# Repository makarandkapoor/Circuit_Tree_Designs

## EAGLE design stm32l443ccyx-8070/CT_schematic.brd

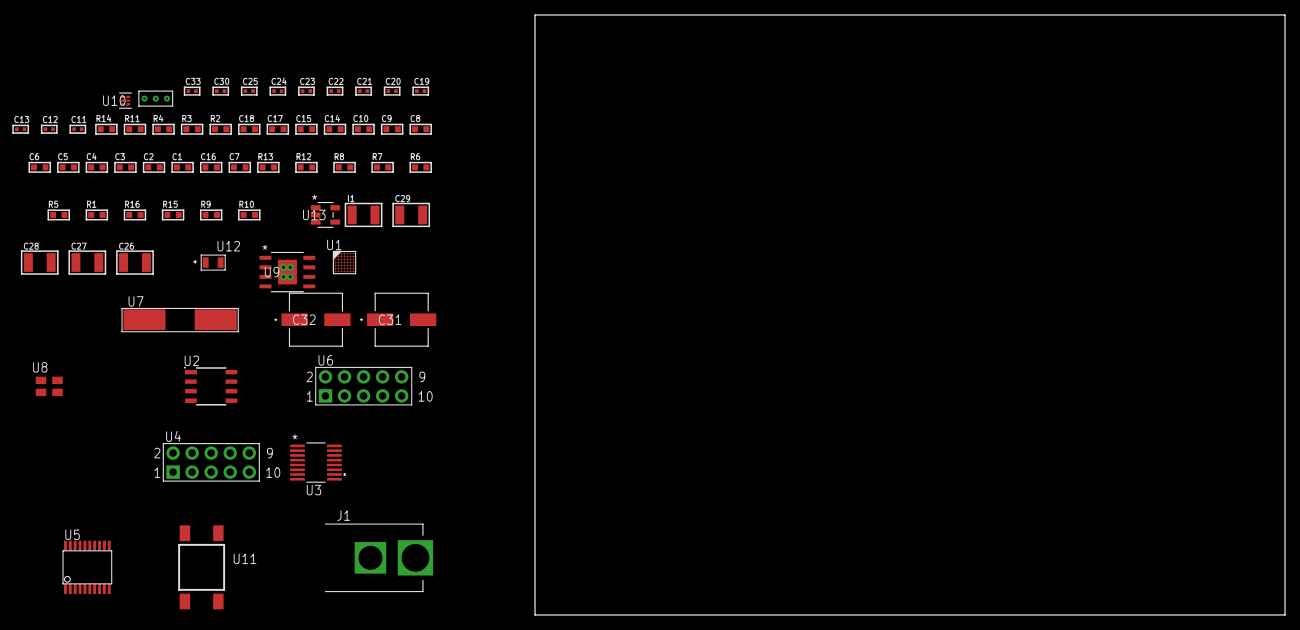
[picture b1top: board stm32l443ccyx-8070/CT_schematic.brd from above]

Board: 2 copper layers, 100.0 x 80.0 mm, 65 parts (0 on the bottom side), 50 nets, no tracks yet.

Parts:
C1, C9, C14, C15, C17, C18: 1e-06; C0603
C2, C3, C4, C5, C6, C10: 1e-07; C0603
C7: 4.7e-06; C0603
C8: 1e-08; C0603
C11, C12: 1e-11; C0402
C13, C25, C33: 1e-08; C0402
C16: 2.2e-07; C0603
C19, C20, C21, C22, C23, C24, C30: 1e-07; C0402
C26, C27, C28, C29: 1e-05; C1210
C31, C32: 0.0001; EXV-9H
I1: 1e-05; L1210
J1: PJ-037B; PJ-037B_PACKAGE
R1, R5, R6, R7, R8, R12, R13: 10000.0; R0603
R2: 1000.0; R0603
R3: 1600.5; R0603
R4: 4700.0; R0603
R9: 100000.0; R0603
R10: 4031.5447154472; R0603
R11: 2200.0; R0603
R14: 9100.0; R0603
R15: 680000.0; R0603
R16: 120000.0; R0603
U1: STM32L443CCY6; WLCSP49
U2: AT25080B-SSHL-T; SOIC-8
U3: LTC2804CGN-1#PBF; SSOP-16
U4, U6: HTSS-105-01-G-D
U5: SP3203ECY-L/TR; TSSOP20-I
U7: ABLS-25.000MHZ-B2F-T
U8: ASEK-32.768KHz-ECST; ASEK
U9: MIC5234YME; SOIC-8_EP
U10: TPS3895ADRYR; SON-6
U11: 4-1437565-2; SW_4-1437565-2
U12: Q65110A2395; LGM67K-G1J2-24-Z
U13: nc7sz125m5x; NC7SZ125M5X
U14: Dummy; DUMMY_PACKAGE_132

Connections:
CLK_CRYSTAL_U1_D6: C11.1, U1.D6, U7.1
CLK_CRYSTAL_U1_D7: C12.1, U1.D7, U7.2
CLK_U1_C7: U1.C7, U8.3
GND: C1.2, C2.2, C3.2, C4.2, C5.2, C6.2, C7.2, C8.2, C9.2, C10.2, C11.2, C12.2, C13.2, C14.2, C15.2, C17.2, C18.2, C19.2, C20.2, C23.2, C24.2, C25.2, C26.2, C27.2, C28.2, C29.2, C30.2, C31.2, C32.2, C33.2, J1.2, R2.2, R5.2, R11.2, R14.2, R16.2, U1.A6, U1.B1, U1.E7, U1.G2, U2.4, U3.8, U4.9, U5.18, U6.9, U8.2, U9.7, U9.EPAD, U10.2, U12.C, U13.1, U13.3, U14.1
NET_U1_A5: R5.1, U1.A5
NET_U1_D5: R4.1, U1.D5, U13.4
NET_U1_G6: R3.1, U1.G6, U12.A
NET_U1_G7: R1.1, U1.G7, U11.3, U11.4
NET_U2_3: R6.1, U2.3
NET_U2_7: R8.1, U2.7
NET_U3_6: C14.1, U3.6
NET_U3_7: C16.1, I1.2, U3.7
NET_U3_9: C15.1, U3.9
NET_U3_10: C16.2, U3.10
NET_U3_11: R9.1, U3.11
NET_U4_3: U3.1, U4.3
NET_U4_4: U3.2, U4.4
NET_U4_5: U3.3, U4.5
NET_U4_6: U3.4, U4.6
NET_U5_1: C21.1, U5.1
NET_U5_2: C23.1, U5.2
NET_U5_3: C21.2, U5.3
NET_U5_4: C22.1, U5.4
NET_U5_5: C22.2, U5.5
NET_U5_6: C24.1, U5.6
NET_U6_3: U5.14, U6.3
NET_U6_4: U5.13, U6.4
NET_U6_5: U5.17, U6.5
NET_U6_6: U5.16, U6.6
NET_U9_4: R10.2, R11.1, U9.4
NET_U10_1: R13.1, R14.1, U10.1
NET_U10_3: R15.2, R16.1, U10.3
NET_U10_4: R12.1, U10.4, U13.2
NET_U11_1: R2.1, U11.1, U11.2
PROC_ADC1_IN11: U1.F4, U14.3
PROC_ADC1_IN16: U1.G4, U14.2
PROC_LPUART1_CTS: U1.E2, U5.8
PROC_LPUART1_RTS: U1.F1, U5.10
PROC_LPUART1_RX: U1.E3, U5.11
PROC_LPUART1_TX: U1.E5, U5.7
PROC_SPI1_MISO: U1.C1, U2.2
PROC_SPI1_MOSI: U1.B4, U2.5
PROC_SPI1_NSS: R7.1, U1.B3, U2.1
PROC_SPI1_SCK: U1.F5, U2.6
PROC_USART1_CTS: U1.A4, U3.13
PROC_USART1_RTS: U1.A3, U3.15
PROC_USART1_RX: U1.C2, U3.16
PROC_USART1_TX: U1.C4, U3.14
VCC_S1_14V2: C26.1, C27.1, C31.1, C32.1, J1.1, U9.5, U9.8
VCC_TIER1_3V3: C1.1, C2.1, C3.1, C4.1, C5.1, C6.1, C7.1, C8.1, C9.1, C10.1, C13.1, C17.1, C18.1, C19.1, C20.1, C25.1, C28.1, C29.1, C30.1, C33.1, I1.1, R1.2, R3.2, R4.2, R6.2, R7.2, R8.2, R9.2, R10.1, R12.2, R13.2, R15.1, U1.A1, U1.A7, U1.B6, U1.F7, U1.G1, U2.8, U3.5, U3.12, U5.12, U5.19, U8.4, U9.1, U10.6, U13.5

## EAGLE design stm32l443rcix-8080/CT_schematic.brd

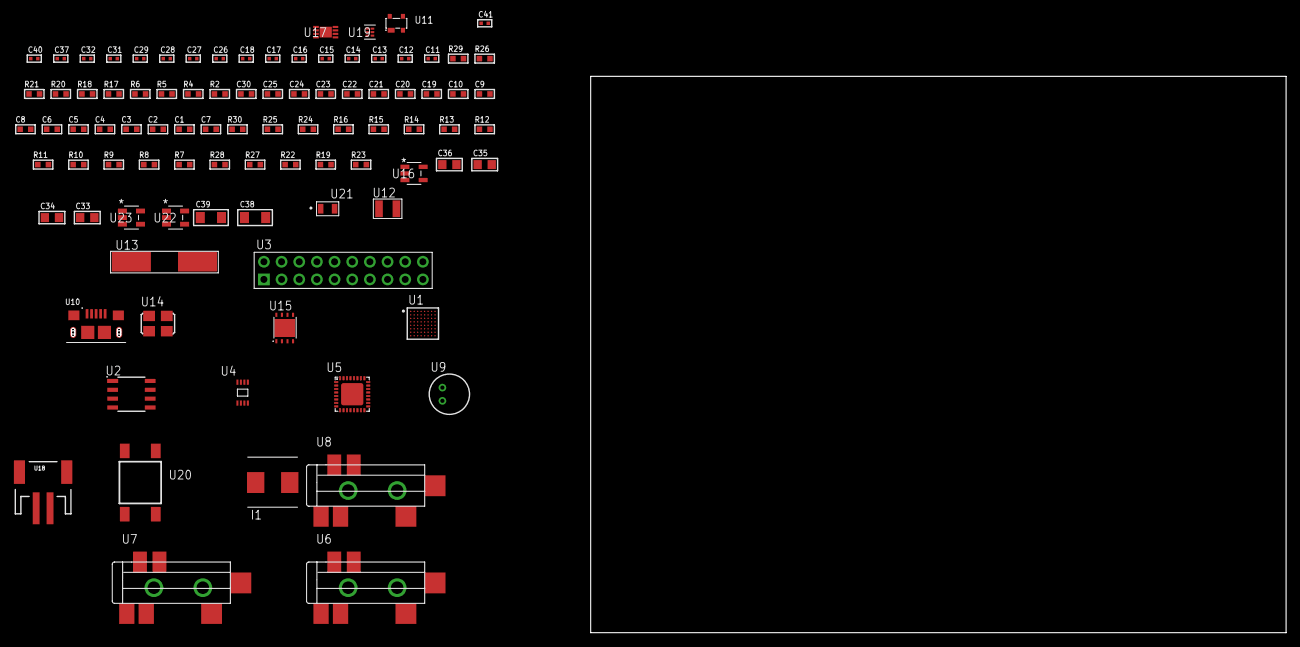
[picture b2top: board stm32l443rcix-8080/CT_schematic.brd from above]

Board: 2 copper layers, 93 parts (0 on the bottom side), 58 nets, no tracks yet.

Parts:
C1, C9, C19, C20, C21, C22, C23, C24, C25, C30: 1e-06; C0603
C2, C3, C4, C5, C6, C10: 1e-07; C0603
C7: 4.7e-06; C0603
C8: 1e-08; C0603
C11, C12, C13, C14: 1e-11; C0402
C15, C18, C31, C32, C40, C41: 1e-08; C0402
C16, C17, C26, C27, C28, C29, C37: 1e-07; C0402
C33, C34, C35, C36: 1e-05; C0805
C38, C39: 1e-05; C1206
I1: 2e-06; WE-HCI_7030/7040/7050
R2, R21: 1000.0; R0603
R4: 4700.0; R0603
R5, R6: 2200.0; R0603
R7, R8, R9, R10, R11, R12, R13, R14, R15, R16, R24, R25, R30: 10000.0; R0603
R17, R18: 1270.0; R0603
R19: 100000.0; R0603
R20: 200.0; R0603
R22: 220000.0; R0603
R23: 1000000.0; R0603
R26: 9100.0; R0603
R27: 680000.0; R0603
R28: 120000.0; R0603
R29: 2000.0; R0603
U1: STM32L443RCI3; UFBGA64
U2: AT25040B-SSHL-T; SOIC-8
U3: TST-110-05-T-D-RA
U4: 24AA08T-I/MNY; TDFN-8/6MM
U5: SGTL5000XNAA3; QFN-32
U6, U7, U8: SJ-43515TS-SMT-TR
U9: WM-64PCT; WM-64PC
U10: 10118193-0001LF; FCI_10118193-0001LF
U11: prtr5v0u2ax; SOT143B
U12: ABS07-32.768KHZ-7-T
U13: ABLS-25.000MHZ-B2F-T
U14: ASFL-24.57MHZ-NCS; ASFL1
U15: LP3878SDX-ADJ/NOPB; WSON-8
U16: ltc3406es5; TSOT-23-5
U17: MCP73831T-2ACI/MC; DFN8_2X3MC
U18: S2B-PH-SM4-TB(LF)(SN); JST-2-SMD
U19: TPS3895ADRYR; SON-6
U20: 4-1437565-2; SW_4-1437565-2
U21: Q65110A2395; LGM67K-G1J2-24-Z
U22, U23: nc7sz125m5x; NC7SZ125M5X

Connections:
CLK_CRYSTAL_U1_A1: C11.1, U1.A1, U12.1
CLK_CRYSTAL_U1_B1: C12.1, U1.B1, U12.2
CLK_CRYSTAL_U1_C1: C13.1, U1.C1, U13.1
CLK_CRYSTAL_U1_D1: C14.1, U1.D1, U13.2
CLK_U5_21: U5.21, U14.3
GND: C1.2, C2.2, C3.2, C4.2, C5.2, C6.2, C7.2, C8.2, C9.2, C10.2, C11.2, C12.2, C13.2, C14.2, C15.2, C16.2, C17.2, C18.2, C26.2, C27.2, C28.2, C29.2, C30.2, C31.2, C32.2, C33.2, C34.2, C35.2, C36.1, C36.2, C37.2, C38.2, C39.2, C40.2, C41.2, R2.2, R7.2, R16.2, R18.2, R21.2, R22.2, R26.2, R28.2, R29.2, U1.C2, U1.D4, U1.D5, U1.D6, U1.F1, U2.4, U3.4, U3.6, U3.8, U3.10, U3.12, U3.14, U3.16, U3.18, U3.20, U4.4, U4.7, U5.1, U5.3, U5.7, U5.EXP, U7.1, U8.1, U9.2, U10.5, U10.6, U10.7, U10.8, U10.9, U11.1, U14.2, U15.3, U15.PAD, U16.2, U17.6, U17.9, U18.2, U19.2, U21.C, U22.2, U22.3, U23.1, U23.3
INPUT_USBPOWER_5V: C38.1, R30.2, U10.1, U11.4, U17.1, U17.2
NET_U1_A3: R6.1, U1.A3, U4.5
NET_U1_B3: R5.1, U1.B3, U4.6
NET_U1_B4: R7.1, U1.B4
NET_U1_E1: R4.1, U1.E1, U23.4
NET_U1_H8: U20.3, U20.4
NET_U2_3: R8.1, U2.3
NET_U2_7: R10.1, U2.7
NET_U3_19: R16.1, U3.19
NET_U5_10: C29.1, U5.10
NET_U5_29: R17.1, U5.29
NET_U5_31: R18.1, U5.31
NET_U6_1: U5.4, U6.1
NET_U6_2: U5.2, U6.2
NET_U6_5: U5.6, U6.5
NET_U7_2: C20.1, U7.2
NET_U7_5: C19.1, U7.5
NET_U8_2: C22.1, C23.1, U8.2
NET_U8_5: C21.1, U8.5
NET_U8_13: C22.2, C23.2
NET_U9_1: C24.1, C25.1, C30.1, U5.16, U9.1
NET_U9_15: C24.2, C25.2
NET_U15_1: C32.1, U15.1
NET_U15_6: R20.2, R21.1, U15.6
NET_U15_8: R19.1, U15.8
NET_U16_3: I1.1, U16.3
NET_U16_5: R22.1, R23.1, U16.5
NET_U16_ATNET_3: I1.2, R23.2
NET_U17_5: R30.1, U17.5
NET_U17_8: R29.1, U17.8
NET_U19_1: R25.1, R26.1, U19.1
NET_U19_3: R27.2, R28.1, U19.3
NET_U19_4: R24.1, U19.4, U22.4, U23.2
NET_U20_1: R2.1, U20.1, U20.2
PROC_SAI1_FS_A: U1.C7, U5.23
PROC_SAI1_SCK_A: U1.D7, U5.24
PROC_SAI1_SD_A: U1.C6, U5.26
PROC_SPI1_MISO: U1.G4, U2.2
PROC_SPI1_MOSI: U1.C4, U2.5
PROC_SPI1_NSS: R9.1, U1.F5, U2.1
PROC_SPI1_SCK: U1.F4, U2.6
PROC_SYS_JTCK_SWCLK: R14.1, U1.A7, U3.9
PROC_SYS_JTDI: R12.1, U1.A6, U3.5
PROC_SYS_JTDO_SWO: U1.A5, U3.13
PROC_SYS_JTMS_SWDIO: R13.1, U1.A8, U3.7
PROC_SYS_JTRST: R11.1, U1.A4, U3.3
PROC_USB_DM: U1.C8, U10.2, U11.3
PROC_USB_DP: U1.B8, U10.3, U11.2
RST_OUT_U3_SRESET_B: R15.1, U3.15, U22.1
VCC_S1_3V7: C33.1, C35.1, C39.1, R19.2, U15.4, U16.4, U17.3, U17.4, U18.1
VCC_TIER1_1V2: C26.1, C34.1, R20.1, U5.30, U15.5
VCC_TIER1_3V3: C1.1, C2.1, C3.1, C4.1, C5.1, C6.1, C7.1, C8.1, C9.1, C10.1, C15.1, C16.1, C17.1, C18.1, C27.1, C28.1, C31.1, C36.2, C37.1, C40.1, C41.1, I1.2, R4.2, R5.2, R6.2, R8.2, R9.2, R10.2, R11.2, R12.2, R13.2, R14.2, R15.2, R17.2, R23.2, R24.2, R25.2, R27.1, U1.B2, U1.D2, U1.E4, U1.E5, U1.E6, U1.H1, U2.8, U3.1, U3.2, U4.8, U5.5, U5.20, U14.4, U19.6, U22.5, U23.5

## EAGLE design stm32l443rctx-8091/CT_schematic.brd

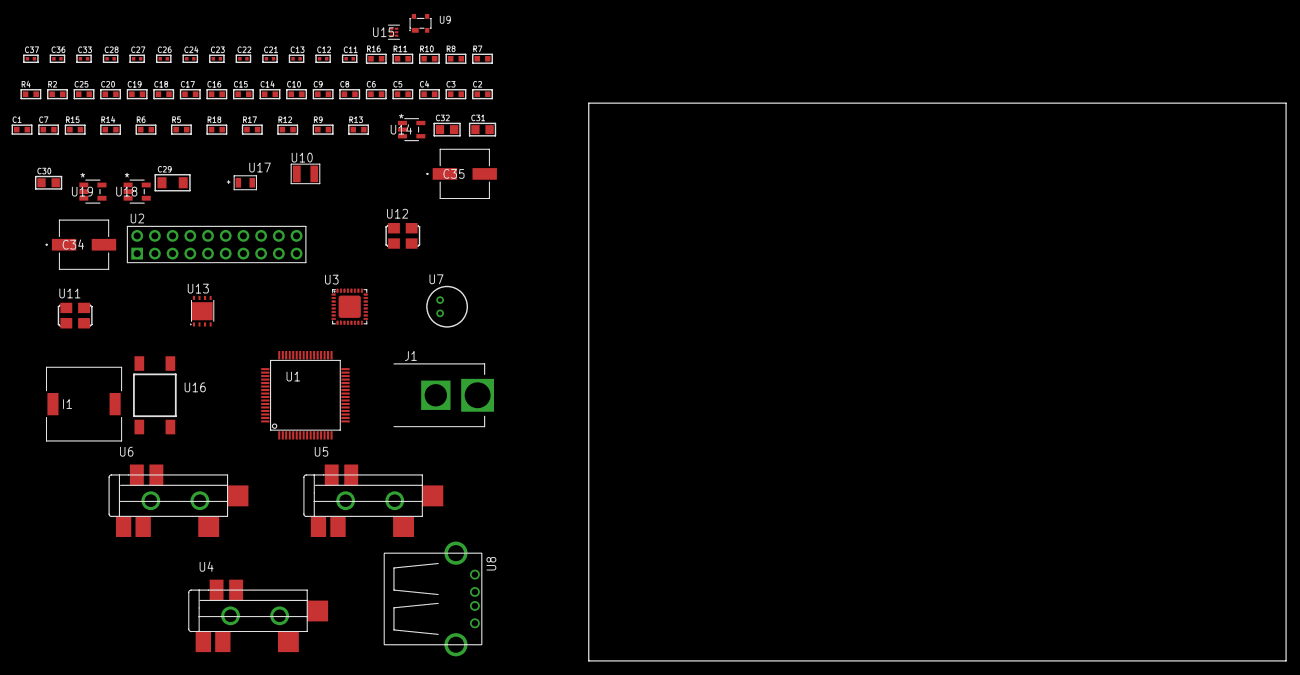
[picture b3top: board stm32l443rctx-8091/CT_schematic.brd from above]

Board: 2 copper layers, 100.0 x 80.0 mm, 74 parts (0 on the bottom side), 44 nets, no tracks yet.

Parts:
C1, C9, C14, C15, C16, C17, C18, C19, C20, C25: 1e-06; C0603
C2, C3, C4, C5, C6, C10: 1e-07; C0603
C7: 4.7e-06; C0603
C8: 1e-08; C0603
C11, C12: 1e-11; C0402
C13, C21, C22, C23, C24, C33: 1e-07; C0402
C26, C27, C28, C36, C37: 1e-08; C0402
C29: 1e-05; C1206
C30, C31, C32: 1e-05; C0805
C34, C35: 0.0001; EXV-9H
I1: 5.2e-06; DR1040
J1: PJ-037B; PJ-037B_PACKAGE
R2, R11: 1000.0; R0603
R4: 4700.0; R0603
R5, R6, R14, R15: 10000.0; R0603
R7, R8: 1270.0; R0603
R9: 100000.0; R0603
R10: 200.0; R0603
R12: 220000.0; R0603
R13: 1000000.0; R0603
R16: 9100.0; R0603
R17: 680000.0; R0603
R18: 120000.0; R0603
U1: STM32L443RCT6; LQFP64
U2: TST-110-05-T-D-RA
U3: SGTL5000XNAA3; QFN-32
U4, U5, U6: SJ-43515TS-SMT-TR
U7: WM-64PCT; WM-64PC
U8: 61400416021; USB-A-H
U9: prtr5v0u2ax; SOT143B
U10: ABS07-32.768KHZ-7-T
U11: ASFL-24.57MHZ-NCS; ASFL1
U12: ASFL1-25MHZ-NCS; ASFL1
U13: LP3878SDX-ADJ/NOPB; WSON-8
U14: ltc3406es5; TSOT-23-5
U15: TPS3895ADRYR; SON-6
U16: 4-1437565-2; SW_4-1437565-2
U17: Q65110A2395; LGM67K-G1J2-24-Z
U18, U19: nc7sz125m5x; NC7SZ125M5X

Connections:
CLK_CRYSTAL_U1_3: C11.1, U1.3, U10.1
CLK_CRYSTAL_U1_4: C12.1, U1.4, U10.2
CLK_U1_5: U1.5, U12.3
CLK_U3_21: U3.21, U11.3
GND: C1.2, C2.2, C3.2, C4.2, C5.2, C6.2, C7.2, C8.2, C9.2, C10.2, C11.2, C12.2, C13.2, C21.2, C22.2, C23.2, C24.2, C25.2, C26.2, C27.2, C28.2, C29.2, C30.2, C31.2, C32.1, C32.2, C33.2, C34.2, C35.2, C36.2, C37.2, J1.2, R2.2, R5.2, R8.2, R11.2, R12.2, R16.2, R18.2, U1.12, U1.18, U1.31, U1.47, U1.63, U2.4, U2.6, U2.8, U2.10, U2.12, U2.14, U2.16, U2.18, U2.20, U3.1, U3.3, U3.7, U3.EXP, U5.1, U6.1, U7.2, U8.4, U8.5, U8.6, U9.1, U11.2, U12.2, U13.3, U13.PAD, U14.2, U15.2, U17.C, U18.2, U18.3, U19.1, U19.3
NET_U1_7: R4.1, U1.7, U19.4
NET_U1_60: R5.1, U1.60
NET_U1_62: U16.3, U16.4
NET_U3_10: C24.1, U3.10
NET_U3_29: R7.1, U3.29
NET_U3_31: R8.1, U3.31
NET_U4_1: U3.4, U4.1
NET_U4_2: U3.2, U4.2
NET_U4_5: U3.6, U4.5
NET_U5_2: C15.1, U5.2
NET_U5_5: C14.1, U5.5
NET_U6_2: C17.1, C18.1, U6.2
NET_U6_5: C16.1, U6.5
NET_U6_13: C17.2, C18.2
NET_U7_1: C19.1, C20.1, C25.1, U3.16, U7.1
NET_U7_15: C19.2, C20.2
NET_U9_4: U8.1, U9.4
NET_U13_1: C28.1, U13.1
NET_U13_6: R10.2, R11.1, U13.6
NET_U13_8: R9.1, U13.8
NET_U14_3: I1.1, U14.3
NET_U14_5: R12.1, R13.1, U14.5
NET_U14_ATNET_3: I1.2, R13.2
NET_U15_1: R15.1, R16.1, U15.1
NET_U15_3: R17.2, R18.1, U15.3
NET_U15_4: R14.1, U15.4, U18.4, U19.2
NET_U16_1: R2.1, U16.1, U16.2
PROC_SAI1_FS_A: U1.33, U3.23
PROC_SAI1_SCK_A: U1.29, U3.24
PROC_SAI1_SD_A: U1.11, U3.26
PROC_SYS_JTCK_SWCLK: U1.49, U2.9
PROC_SYS_JTDO_SWO: U1.55, U2.13
PROC_SYS_JTMS_SWDIO: U1.46, U2.7
PROC_USB_DM: U1.44, U8.2, U9.3
PROC_USB_DP: U1.45, U8.3, U9.2
RST_OUT_U2_SRESET_B: R6.1, U2.15, U18.1
VCC_S1_4V7: C29.1, C31.1, C34.1, C35.1, J1.1, R9.2, U13.4, U14.4
VCC_TIER1_1V2: C21.1, C30.1, R10.1, U3.30, U13.5
VCC_TIER1_3V3: C1.1, C2.1, C3.1, C4.1, C5.1, C6.1, C7.1, C8.1, C9.1, C10.1, C13.1, C22.1, C23.1, C26.1, C27.1, C32.2, C33.1, C36.1, C37.1, I1.2, R4.2, R6.2, R7.2, R13.2, R14.2, R15.2, R17.1, U1.1, U1.13, U1.19, U1.32, U1.48, U1.64, U2.1, U3.5, U3.20, U11.4, U12.4, U15.6, U18.5, U19.5

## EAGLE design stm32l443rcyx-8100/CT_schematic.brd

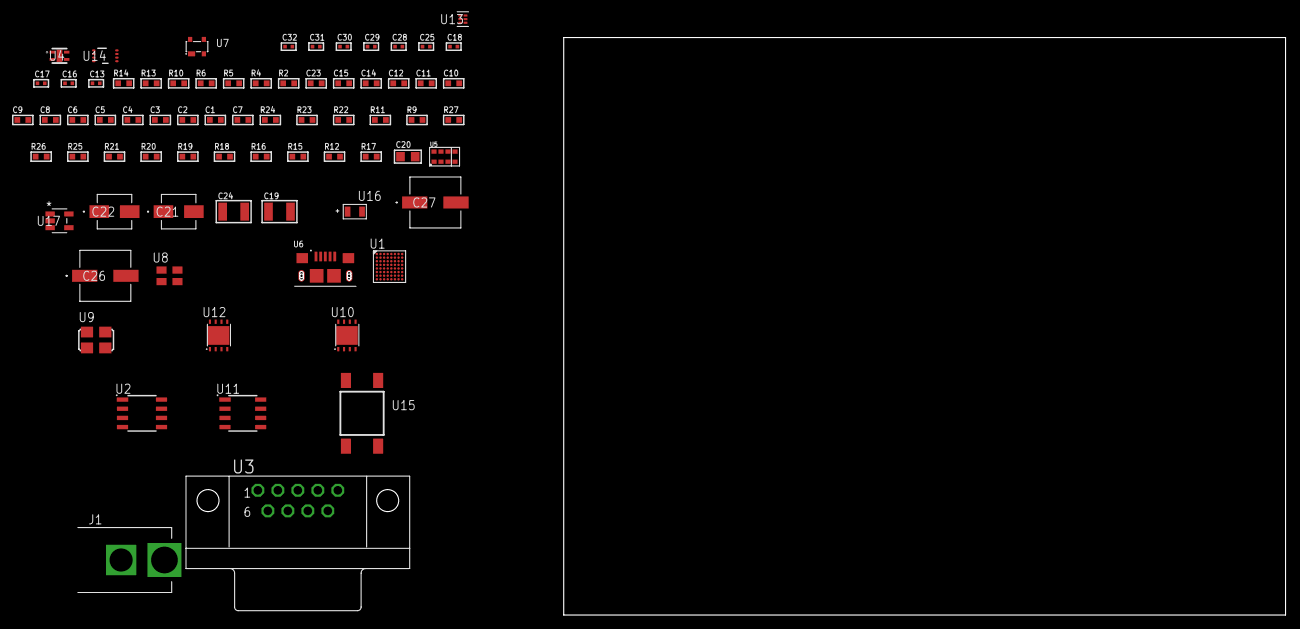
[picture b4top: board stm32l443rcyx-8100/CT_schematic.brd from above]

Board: 2 copper layers, 73 parts (0 on the bottom side), 36 nets, no tracks yet.

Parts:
C1, C9, C11, C12, C14, C15: 1e-06; C0603
C2, C3, C4, C5, C6, C10: 1e-07; C0603
C7: 4.7e-06; C0603
C8: 1e-08; C0603
C13, C25, C29, C31: 1e-07; C0402
C16, C17, C18, C28, C30, C32: 1e-08; C0402
C19, C24: 1e-05; C1210
C20: 1e-05; C0805
C21: 1e-06; EXV-9B
C22: 2.2e-06; EXV-9B
C23: 8e-07; R0603
C26, C27: 0.0001; EXV-9H
J1: PJ-037B; PJ-037B_PACKAGE
R2, R14: 1000.0; R0603
R4: 4700.0; R0603
R5, R6: 2200.0; R0603
R9, R11, R22, R23: 10000.0; R0603
R10: 120.0; R0603
R12, R15, R16, R18, R19, R21: 100000.0; R0603
R13: 806.0; R0603
R17: 164658.62; R0603
R20, R25: 300000.0; R0603
R24: 82000.0; R0603
R26: 120000.0; R0603
R27: 200000.0; R0603
U1: STM32L443RCY6; WLCSP64
U2: MCP2562-E/SN; SOIC-8
U3: 182-009-113R531; 182-009-MALE
U4: Si7034-A10-IM; SI7034-A10-IM
U5: TMD27711; SMD-8
U6: 10118193-0001LF; FCI_10118193-0001LF
U7: prtr5v0u2ax; SOT143B
U8: ASEK-32.768KHz-ECST; ASEK
U9: ASFL1-25MHZ-NCS; ASFL1
U10: LP3878SDX-ADJ/NOPB; WSON-8
U11: LP2954AIMX/NOPB; LP2954
U12: LP2951ACSDX/NOPB; WSON-8
U13: TPS3895ADRYR; SON-6
U14: LSF0102DCTR; DCU0008A_N
U15: 4-1437565-2; SW_4-1437565-2
U16: Q65110A2395; LGM67K-G1J2-24-Z
U17: nc7sz125m5x; NC7SZ125M5X

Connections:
CLK_U1_C8: U1.C8, U8.3
CLK_U1_D8: U1.D8, U9.3
GND: C1.2, C2.2, C3.2, C4.2, C5.2, C6.2, C7.2, C8.2, C9.2, C10.2, C11.2, C12.2, C13.2, C14.2, C15.2, C16.2, C17.2, C18.2, C19.2, C20.2, C21.2, C22.2, C23.2, C24.2, C25.2, C26.2, C27.2, C28.2, C29.2, C30.2, C31.2, C32.2, J1.2, R2.2, R9.2, R14.2, R18.2, R21.2, R24.2, R26.2, U1.A7, U1.B1, U1.F8, U1.H2, U1.H8, U2.2, U2.8, U3.5, U4.5, U5.3, U6.5, U6.6, U6.7, U6.8, U6.9, U7.1, U8.2, U9.2, U10.3, U10.PAD, U11.4, U12.3, U12.4, U12.PAD, U13.2, U14.1, U16.C, U17.1, U17.3
NET_U1_A6: R6.1, U1.A6, U4.4
NET_U1_B5: R5.1, U1.B5, U4.2
NET_U1_C5: R9.1, U1.C5
NET_U1_D6: R4.1, U1.D6, U17.4
NET_U1_H6: U15.3, U15.4
NET_U2_6: R10.2, U2.6
NET_U3_2: R10.2, U2.6, U3.2
NET_U3_3: R10.1, U2.7, U3.3
NET_U5_7: R11.1, U5.7
NET_U7_4: U6.1, U7.4
NET_U10_1: C18.1, U10.1
NET_U10_6: R13.2, R14.1, U10.6
NET_U10_8: R12.1, U10.8
NET_U11_3: R16.1, U11.3
NET_U11_5: R15.1, U11.5
NET_U11_7: R17.2, R18.1, U11.7
NET_U12_5: R19.1, U12.5
NET_U12_7: R20.2, R21.1, U12.7
NET_U13_1: R23.1, R24.1, U13.1
NET_U13_3: R25.2, R26.1, U13.3
NET_U13_4: R22.1, U13.4, U17.2
NET_U14_8: R27.1, U14.8
NET_U15_1: R2.1, U15.1, U15.2
PROC_CAN1_RX: U1.C6, U2.4
PROC_CAN1_TX: U1.B6, U2.1
PROC_I2C2_SCL_TOXCVR: U5.2, U14.5
PROC_I2C2_SDA_TOXCVR: U5.8, U14.6
PROC_USB_DM: U1.D3, U6.2, U7.3
PROC_USB_DP: U1.C1, U6.3, U7.2
VCC_S1_15V9: C19.1, C21.1, C23.1, C26.1, C27.1, J1.1, R12.2, R16.2, U10.4, U11.8, U12.8
VCC_TIER1_1V8: C1.1, C2.1, C3.1, C4.1, C5.1, C6.1, C7.1, C12.1, C13.1, C20.1, C25.1, C30.1, C31.1, C32.1, R4.2, R5.2, R6.2, R13.1, R22.2, R23.2, R25.1, U1.A8, U1.B7, U1.H1, U1.H7, U2.5, U4.1, U10.5, U13.6, U14.2, U17.5
VCC_TIER1_3V3: C8.1, C9.1, C10.1, C14.1, C15.1, C16.1, C17.1, C22.1, C28.1, C29.1, R11.2, R15.2, R17.1, R27.2, U1.A1, U1.G8, U5.1, U5.4, U8.4, U9.4, U11.1, U14.7
VCC_TIER1_5V0: C11.1, C24.1, R19.2, R20.1, U2.3, U12.1

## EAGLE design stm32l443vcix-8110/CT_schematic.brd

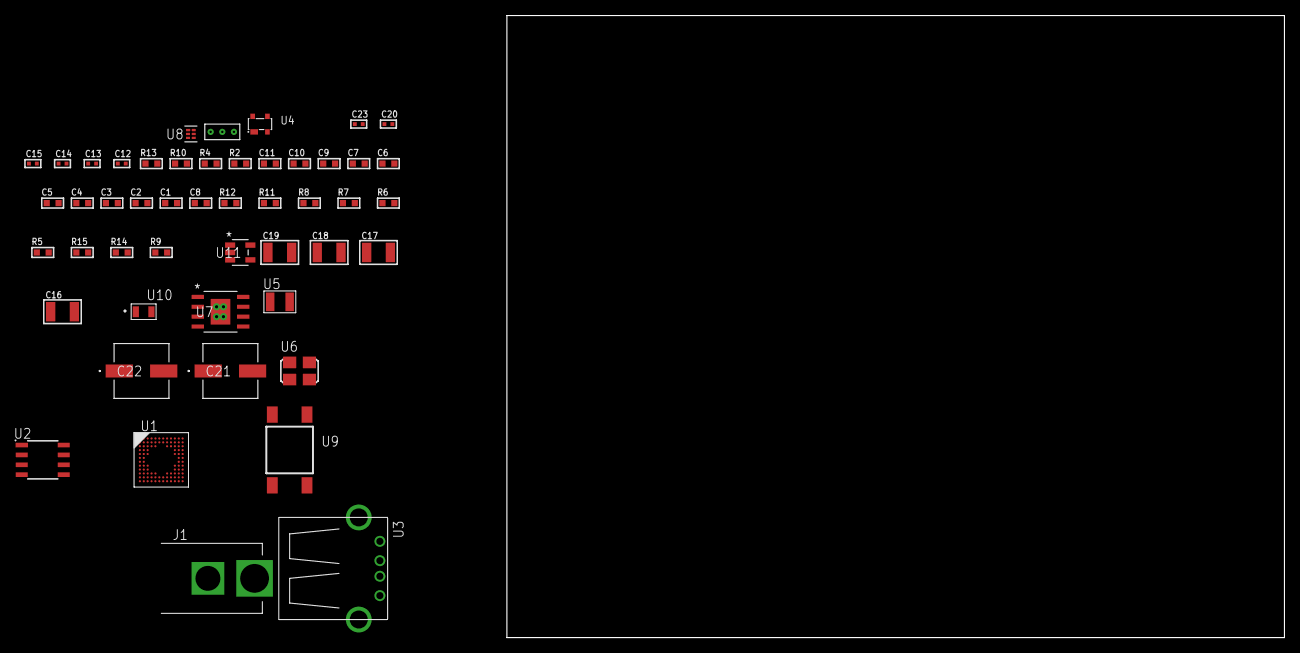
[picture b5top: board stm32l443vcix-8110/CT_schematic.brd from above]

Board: 2 copper layers, 100.0 x 80.0 mm, 49 parts (0 on the bottom side), 25 nets, no tracks yet.

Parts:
C1, C11: 1e-06; C0603
C2, C3, C4, C5, C6, C7, C9: 1e-07; C0603
C8: 4.7e-06; C0603
C10: 1e-08; C0603
C12, C13: 1e-11; C0402
C14, C15, C23: 1e-08; C0402
C16, C17, C18, C19: 1e-05; C1210
C20: 1e-07; C0402
C21, C22: 0.0001; EXV-9H
J1: PJ-037B; PJ-037B_PACKAGE
R2: 1000.0; R0603
R4: 4700.0; R0603
R5, R6, R7, R8, R11, R12: 10000.0; R0603
R9: 4031.5447154472; R0603
R10: 2200.0; R0603
R13: 9100.0; R0603
R14: 680000.0; R0603
R15: 120000.0; R0603
U1: STM32L443VCI6; UFBGA100
U2: AT25640B-SSHL-T; SOIC-8
U3: 61400416021; USB-A-H
U4: prtr5v0u2ax; SOT143B
U5: ABS07-32.768KHZ-7-T
U6: ASFL1-25MHZ-NCS; ASFL1
U7: MIC5234YME; SOIC-8_EP
U8: TPS3895ADRYR; SON-6
U9: 4-1437565-2; SW_4-1437565-2
U10: Q65110A2395; LGM67K-G1J2-24-Z
U11: nc7sz125m5x; NC7SZ125M5X
U12: Dummy; DUMMY_PACKAGE_104

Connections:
CLK_CRYSTAL_U1_D1: C12.1, U1.D1, U5.1
CLK_CRYSTAL_U1_E1: C13.1, U1.E1, U5.2
CLK_U1_F1: U1.F1, U6.3
GND: C1.2, C2.2, C3.2, C4.2, C5.2, C6.2, C7.2, C8.2, C9.2, C10.2, C11.2, C12.2, C13.2, C14.2, C15.2, C16.2, C17.2, C18.2, C19.2, C20.2, C21.2, C22.2, C23.2, J1.2, R2.2, R5.2, R10.2, R13.2, R15.2, U1.D3, U1.E3, U1.F2, U1.F11, U1.F12, U1.J1, U1.K1, U2.4, U3.4, U3.5, U3.6, U4.1, U6.2, U7.7, U7.EPAD, U8.2, U10.C, U11.1, U11.3, U12.1
NET_U1_A4: R5.1, U1.A4
NET_U1_H2: R4.1, U1.H2, U11.4
NET_U1_M12: U9.3, U9.4
NET_U2_3: R6.1, U2.3
NET_U2_7: R8.1, U2.7
NET_U4_4: U3.1, U4.4
NET_U7_4: R9.2, R10.1, U7.4
NET_U8_1: R12.1, R13.1, U8.1
NET_U8_3: R14.2, R15.1, U8.3
NET_U8_4: R11.1, U8.4, U11.2
NET_U9_1: R2.1, U9.1, U9.2
PROC_PE1: U1.A2, U12.3
PROC_PE3: U1.A1, U12.2
PROC_SPI1_MISO: U1.A7, U2.2
PROC_SPI1_MOSI: U1.C5, U2.5
PROC_SPI1_NSS: R7.1, U1.A9, U2.1
PROC_SPI1_SCK: U1.A8, U2.6
PROC_USB_DM: U3.2, U4.3
PROC_USB_DP: U3.3, U4.2
VCC_S1_5V2: C16.1, C17.1, C21.1, C22.1, J1.1, U7.5, U7.8
VCC_TIER1_3V3: C1.1, C2.1, C3.1, C4.1, C5.1, C6.1, C7.1, C8.1, C9.1, C10.1, C11.1, C14.1, C15.1, C18.1, C19.1, C20.1, C23.1, R4.2, R6.2, R7.2, R8.2, R9.1, R11.2, R12.2, R14.1, U1.C4, U1.C11, U1.E2, U1.G2, U1.G11, U1.G12, U1.H3, U1.L1, U1.M1, U2.8, U6.4, U7.1, U8.6, U11.5

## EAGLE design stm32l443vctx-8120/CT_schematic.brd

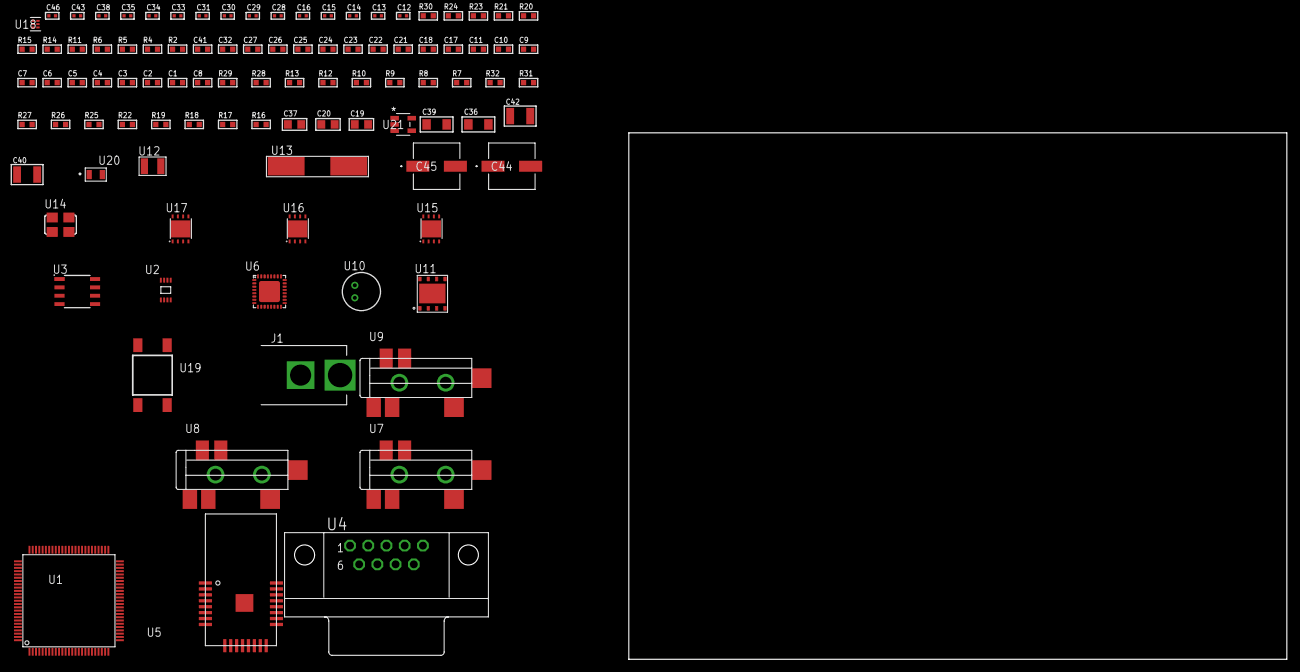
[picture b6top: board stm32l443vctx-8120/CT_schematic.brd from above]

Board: 2 copper layers, 100.0 x 80.0 mm, 98 parts (0 on the bottom side), 59 nets, no tracks yet.

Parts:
C1, C11, C17, C18, C21, C22, C23, C24, C25, C26, C27, C32, C41: 1e-06; C0603
C2, C3, C4, C5, C6, C7, C9: 1e-07; C0603
C8: 4.7e-06; C0603
C10: 1e-08; C0603
C12, C13, C14, C15: 1e-11; C0402
C16, C34, C35, C38, C46: 1e-08; C0402
C19, C20, C37: 1e-05; C0805
C28, C29, C30, C31, C33, C43: 1e-07; C0402
C36, C39: 1e-05; C1206
C40, C42: 1e-05; C1210
C44, C45: 0.0001; EXV-9H
J1: PJ-037B; PJ-037B_PACKAGE
R2, R21, R24: 1000.0; R0603
R4: 4700.0; R0603
R5, R6: 2200.0; R0603
R7, R8, R9, R10, R12, R13, R28, R29: 10000.0; R0603
R11: 120.0; R0603
R14, R15: 1270.0; R0603
R16, R17, R18, R19, R22, R25, R27: 100000.0; R0603
R20: 200.0; R0603
R23: 2231.0; R0603
R26: 300000.0; R0603
R30: 9100.0; R0603
R31: 680000.0; R0603
R32: 120000.0; R0603
U1: STM32L443VCT6; LQFP100
U2: 24AA64T-I/MNY; TDFN-8/6MM
U3: MCP2562-E/SN; SOIC-8
U4: 182-009-113R531; 182-009-MALE
U5: ATBTLC1000-MR110CA
U6: SGTL5000XNAA3; QFN-32
U7, U8, U9: SJ-43515TS-SMT-TR
U10: WM-64PCT; WM-64PC
U11: SST26VF064B-104I/MF; WFDN-8
U12: ABS07-32.768KHZ-7-T
U13: ABLS-25.000MHZ-B2F-T
U14: ASFL-24.57MHZ-NCS; ASFL1
U15, U16: LP3878SDX-ADJ/NOPB; WSON-8
U17: LP2951ACSDX/NOPB; WSON-8
U18: TPS3895ADRYR; SON-6
U19: 4-1437565-2; SW_4-1437565-2
U20: Q65110A2395; LGM67K-G1J2-24-Z
U21: nc7sz125m5x; NC7SZ125M5X

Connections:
CLK_CRYSTAL_U1_8: C12.1, U1.8, U12.1
CLK_CRYSTAL_U1_9: C13.1, U1.9, U12.2
CLK_CRYSTAL_U1_12: C14.1, U1.12, U13.1
CLK_CRYSTAL_U1_13: C15.1, U1.13, U13.2
CLK_U6_21: U6.21, U14.3
GND: C1.2, C2.2, C3.2, C4.2, C5.2, C6.2, C7.2, C8.2, C9.2, C10.2, C11.2, C12.2, C13.2, C14.2, C15.2, C16.2, C17.2, C18.2, C19.2, C20.2, C28.2, C29.2, C30.2, C31.2, C32.2, C33.2, C34.2, C35.2, C36.2, C37.2, C38.2, C39.2, C40.2, C41.2, C42.2, C43.2, C44.2, C45.2, C46.2, J1.2, R2.2, R7.2, R8.2, R10.2, R15.2, R21.2, R24.2, R27.2, R30.2, R32.2, U1.10, U1.19, U1.20, U1.27, U1.49, U1.74, U1.99, U2.4, U2.7, U3.2, U3.8, U4.5, U5.1, U5.9, U5.13, U5.24, U5.25, U6.1, U6.3, U6.7, U6.EXP, U8.1, U9.1, U10.2, U11.4, U11.9, U14.2, U15.3, U15.PAD, U16.3, U16.PAD, U17.3, U17.4, U17.PAD, U18.2, U20.C, U21.1, U21.3
NET_U1_14: R4.1, U1.14, U21.4
NET_U1_68: R5.1, U1.68, U2.6
NET_U1_69: R6.1, U1.69, U2.5
NET_U1_94: R7.1, U1.94
NET_U1_98: U19.3, U19.4
NET_U2_1: R8.1, U2.1
NET_U2_2: R9.1, U2.2
NET_U2_3: R10.1, U2.3
NET_U3_6: R11.2, U3.6
NET_U4_2: R11.2, U3.6, U4.2
NET_U4_3: R11.1, U3.7, U4.3
NET_U5_17: R12.1, U5.17
NET_U5_20: R13.1, U5.20
NET_U6_10: C31.1, U6.10
NET_U6_29: R14.1, U6.29
NET_U6_31: R15.1, U6.31
NET_U7_1: U6.4, U7.1
NET_U7_2: U6.2, U7.2
NET_U7_5: U6.6, U7.5
NET_U8_2: C22.1, U8.2
NET_U8_5: C21.1, U8.5
NET_U9_2: C24.1, C25.1, U9.2
NET_U9_5: C23.1, U9.5
NET_U9_13: C24.2, C25.2
NET_U10_1: C26.1, C27.1, C32.1, U6.16, U10.1
NET_U10_15: C26.2, C27.2
NET_U15_1: C35.1, U15.1
NET_U15_6: R20.2, R21.1, U15.6
NET_U15_8: R19.1, U15.8
NET_U16_1: C38.1, U16.1
NET_U16_6: R23.2, R24.1, U16.6
NET_U16_8: R22.1, U16.8
NET_U17_5: R25.1, U17.5
NET_U17_7: R26.2, R27.1, U17.7
NET_U18_1: R29.1, R30.1, U18.1
NET_U18_3: R31.2, R32.1, U18.3
NET_U18_4: R28.1, U18.4, U21.2
NET_U19_1: R2.1, U19.1, U19.2
PROC_CAN1_RX: U1.70, U3.4
PROC_CAN1_TX: U1.71, U3.1
PROC_QUADSPI_BK1_IO0: U1.36, U11.5
PROC_QUADSPI_BK1_IO1: U1.35, U11.2
PROC_QUADSPI_BK1_IO2: R17.1, U1.32, U11.3
PROC_QUADSPI_BK1_IO3: R18.1, U1.31, U11.7
PROC_QUADSPI_BK1_NCS: R16.1, U1.25, U11.1
PROC_QUADSPI_CLK: U1.26, U11.6
PROC_SAI1_FS_A: U1.3, U6.23
PROC_SAI1_SCK_A: U1.4, U6.24
PROC_SAI1_SD_A: U1.5, U6.26
VCC_S1_10V1: C36.1, C39.1, C41.1, C44.1, C45.1, J1.1, R19.2, R22.2, U15.4, U16.4, U17.8
VCC_TIER1_1V2: C28.1, C37.1, R20.1, U6.30, U15.5
VCC_TIER1_3V3: C1.1, C2.1, C3.1, C4.1, C5.1, C6.1, C7.1, C8.1, C9.1, C10.1, C11.1, C16.1, C18.1, C19.1, C20.1, C29.1, C30.1, C33.1, C34.1, C40.1, C43.1, C46.1, R4.2, R5.2, R6.2, R9.2, R12.2, R13.2, R14.2, R16.2, R17.2, R18.2, R23.1, R28.2, R29.2, R31.1, U1.6, U1.11, U1.21, U1.22, U1.28, U1.50, U1.73, U1.75, U1.100, U2.8, U3.5, U5.6, U5.22, U6.5, U6.20, U11.8, U14.4, U16.5, U18.6, U21.5
VCC_TIER1_5V0: C17.1, C42.1, R25.2, R26.1, U3.3, U17.1

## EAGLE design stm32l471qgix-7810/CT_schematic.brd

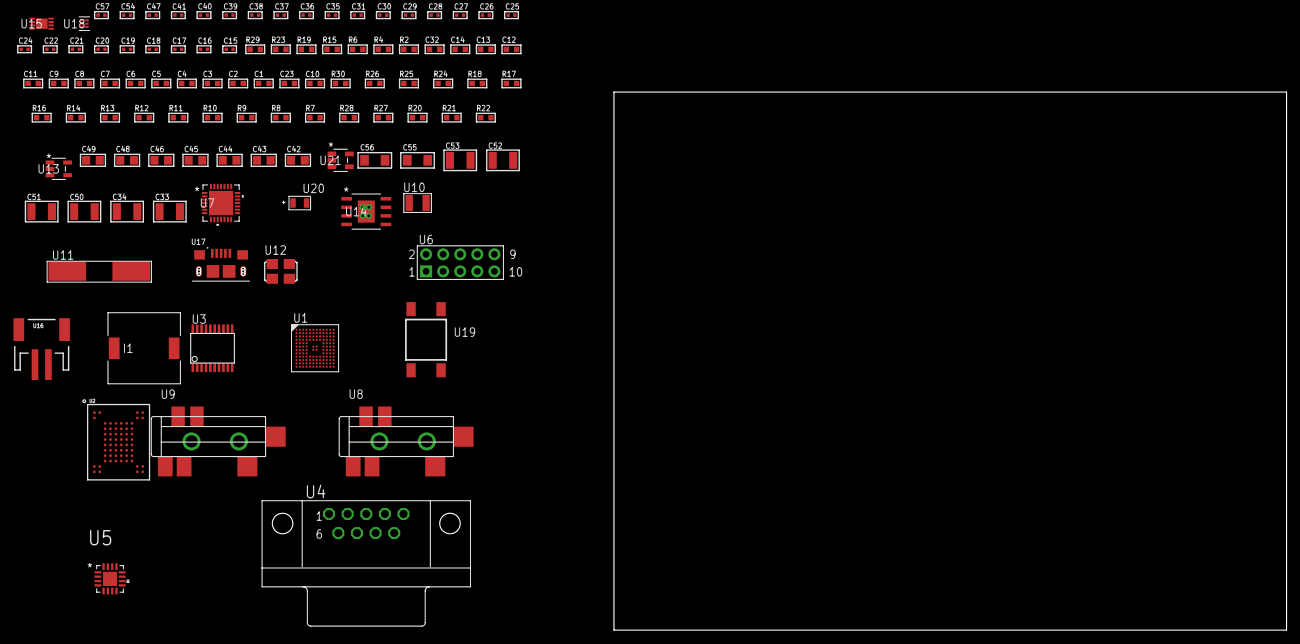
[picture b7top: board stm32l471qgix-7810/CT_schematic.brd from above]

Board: 2 copper layers, 106 parts (0 on the bottom side), 68 nets, no tracks yet.

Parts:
C1, C14, C32: 1e-06; C0603
C2, C3, C4, C5, C6, C7, C8, C9, C11, C12: 1e-07; C0603
C10: 4.7e-06; C0603
C13: 1e-08; C0603
C15, C16, C17, C18: 1e-11; C0402
C19, C20, C21, C22, C24, C25, C26, C27, C28, C29, C30, C31, C37, C38, C39, C40, C41, C54: 1e-07; C0402
C23: 2.2e-06; C0603
C33, C34: 2.2e-05; C1210
C35, C36: 1e-09; C0402
C42, C43, C44, C45, C46, C48, C49: 1e-05; C0805
C47, C57: 1e-08; C0402
C50, C51, C52, C53: 1e-05; C1210
C55, C56: 1e-05; C1206
I1: 7e-06; DR1040
R2: 1000.0; R0603
R4: 4700.0; R0603
R6, R23: 2200.0; R0603
R7, R8, R9, R10, R11, R12, R13, R14, R24, R25, R30: 10000.0; R0603
R15: 47.0; R0603
R16, R17, R18: 47000.0; R0603
R19: 680.0; R0603
R20: 490000.0; R0603
R21: 1000000.0; R0603
R22: 4031.5447154472; R0603
R26: 82000.0; R0603
R27: 300000.0; R0603
R28: 120000.0; R0603
R29: 2000.0; R0603
U1: STM32L471QGI6; UFBGA132
U2: mt29f4g08abbdah4; VFBGA-63
U3: SP3203ECY-L/TR; TSSOP20-I
U4: 182-009-113R531; 182-009-MALE
U5: TSC2013QRSARQ1; QFN65P400X400X100-17N
U6: HTSS-105-01-G-D
U7: WM8731CLSEFL; QFN-28
U8, U9: SJ-43515TS-SMT-TR
U10: ABS07-32.768KHZ-7-T
U11: ABLS-25.000MHZ-B2F-T
U12: ASFL1-12.288MHZ-EC-T; ASFL1
U13: ltc3406es5; TSOT-23-5
U14: MIC5234YME; SOIC-8_EP
U15: MCP73831T-2ACI/MC; DFN8_2X3MC
U16: S2B-PH-SM4-TB(LF)(SN); JST-2-SMD
U17: 10118193-0001LF; FCI_10118193-0001LF
U18: TPS3895ADRYR; SON-6
U19: 4-1437565-2; SW_4-1437565-2
U20: Q65110A2395; LGM67K-G1J2-24-Z
U21: nc7sz125m5x; NC7SZ125M5X

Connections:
CLK_CRYSTAL_U1_D1: C15.1, U1.D1, U10.1
CLK_CRYSTAL_U1_E1: C16.1, U1.E1, U10.2
CLK_CRYSTAL_U1_F1: C17.1, U1.F1, U11.1
CLK_CRYSTAL_U1_G1: C18.1, U1.G1, U11.2
CLK_U7_1: U7.1, U12.3
GND: C1.2, C2.2, C3.2, C4.2, C5.2, C6.2, C7.2, C8.2, C9.2, C10.2, C11.2, C12.2, C13.2, C14.2, C15.2, C16.2, C17.2, C18.2, C19.2, C20.2, C21.2, C22.2, C23.2, C24.2, C25.2, C28.2, C29.2, C36.2, C37.2, C38.2, C39.2, C40.2, C41.2, C42.2, C43.2, C44.2, C45.2, C46.2, C47.2, C48.2, C49.1, C49.2, C50.2, C51.2, C52.2, C53.2, C54.2, C55.2, C56.2, C57.2, R2.2, R7.2, R16.2, R17.2, R18.2, R20.2, R23.2, R26.2, R28.2, R29.2, U1.D3, U1.E3, U1.F2, U1.F6, U1.F7, U1.F11, U1.F12, U1.J1, U2.C5, U2.F7, U2.K3, U2.K8, U3.18, U4.5, U5.17, U6.9, U7.4, U7.15, U7.19, U7.25, U7.26, U7.29, U8.1, U9.1, U12.2, U13.2, U14.7, U14.EPAD, U15.6, U15.9, U16.2, U17.5, U17.6, U17.7, U17.8, U17.9, U18.2, U20.C, U21.1, U21.3
INPUT_USBPOWER_5V: C55.1, R30.2, U15.1, U15.2, U17.1
NET_U1_A4: R7.1, U1.A4
NET_U1_B3: R6.1, U1.B3, U5.1
NET_U1_H2: R4.1, U1.H2, U21.4
NET_U1_M12: U19.3, U19.4
NET_U2_C3: R12.1, U2.C3
NET_U3_1: C26.1, U3.1
NET_U3_2: C28.1, U3.2
NET_U3_3: C26.2, U3.3
NET_U3_4: C27.1, U3.4
NET_U3_5: C27.2, U3.5
NET_U3_6: C29.1, U3.6
NET_U4_2: U3.14, U4.2
NET_U4_3: U3.17, U4.3
NET_U4_7: U3.13, U4.7
NET_U4_8: U3.16, U4.8
NET_U5_4: R14.1, U5.4
NET_U5_5: R13.1, U5.5
NET_U5_9: C30.2, C31.2, C32.2, R15.2, U5.9
NET_U5_15: R15.1, U5.8, U5.15
NET_U6_3: U5.12, U6.3
NET_U6_4: U5.14, U6.4
NET_U6_5: U5.11, U6.5
NET_U6_6: U5.13, U6.6
NET_U7_20: C41.1, C46.1, U7.20
NET_U8_2: C34.1, R17.1, U8.2
NET_U8_5: C33.1, R16.1, U8.5
NET_U9_5: C35.1, C36.1, R18.1, R19.1, U9.5
NET_U13_3: I1.1, U13.3
NET_U13_5: R20.1, R21.1, U13.5
NET_U13_ATNET_3: I1.2, R21.2
NET_U14_4: R22.2, R23.1, U14.4
NET_U15_5: R30.1, U15.5
NET_U15_8: R29.1, U15.8
NET_U18_1: R25.1, R26.1, U18.1
NET_U18_3: R27.2, R28.1, U18.3
NET_U18_4: R24.1, U18.4, U21.2
NET_U19_1: R2.1, U19.1, U19.2
PROC_FMC_A16: U1.J11, U2.D5
PROC_FMC_A17: U1.J10, U2.C4
PROC_FMC_D0: U1.H11, U2.H4
PROC_FMC_D1: U1.H10, U2.J4
PROC_FMC_D2: U1.C9, U2.K4
PROC_FMC_D3: U1.B9, U2.K5
PROC_FMC_D4: U1.M7, U2.K6
PROC_FMC_D5: U1.L7, U2.J7
PROC_FMC_D6: U1.M8, U2.K7
PROC_FMC_D7: U1.L8, U2.J8
PROC_FMC_INT3: R8.1, U1.H4, U2.C8
PROC_FMC_NCE3: R9.1, U1.D9, U2.C6
PROC_FMC_NOE: R11.1, U1.B7, U2.D4
PROC_FMC_NWE: R10.1, U1.A6, U2.C7
PROC_LPUART1_CTS: U1.E9, U3.8
PROC_LPUART1_RTS: U1.G4, U3.10
PROC_LPUART1_RX: U1.H1, U3.11
PROC_LPUART1_TX: U1.J2, U3.7
PROC_SAI1_FS_A: U1.B1, U7.9, U7.11
PROC_SAI1_SCK_A: U1.C2, U7.7
PROC_SAI1_SD_A: U1.B6, U7.8
VCC_S1_3V7: C48.1, C50.1, C51.1, C56.1, U13.4, U14.5, U14.8, U15.3, U15.4, U16.1
VCC_TIER1_1V8: C1.1, C2.1, C3.1, C4.1, C5.1, C6.1, C7.1, C8.1, C9.1, C10.1, C11.1, C12.1, C19.1, C20.1, C21.1, C22.1, C23.1, C25.1, C30.1, C37.1, C38.1, C39.1, C40.1, C42.1, C43.1, C44.1, C45.1, C49.2, C54.1, C57.1, I1.2, R4.2, R6.2, R8.2, R9.2, R10.2, R11.2, R12.2, R13.2, R14.2, R21.2, R24.2, R25.2, R27.1, U1.C4, U1.C11, U1.E2, U1.G2, U1.G6, U1.G7, U1.G11, U1.G12, U1.H3, U2.D3, U2.G4, U2.H8, U2.J6, U3.12, U5.7, U7.3, U7.5, U7.12, U7.18, U18.6, U21.5
VCC_TIER1_3V3: C13.1, C14.1, C24.1, C31.1, C32.1, C47.1, C52.1, C53.1, R22.1, U1.L1, U1.M1, U3.19, U5.10, U12.4, U14.1
